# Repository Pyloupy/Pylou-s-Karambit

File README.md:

# Pylou-s-Karambit

Hey there ! This is the GitHub Repo where I'll show my creation based of the Reaver Karambit from Valorant (cf photo down below) that I wanted to bring to life!

I tried to make it as realistic as possible with LEDs A smoke generator and even movement and voice recognition!  You should see everything here that will make you able to recreate my work, GL :)
# Why ?
Well, you should first know that my work is completly useless and is purely aesthetic. It'll be able to cut butter at his peak or maybe set my house in fire if I did my job wrong ;-;

I wanted to make it as a fan of the game Valorant. A lot of recreation has been made because it is a very popular weapon skin in the game, but none tried to push the reality to the maximum, thats why I'm here !

At first, I created a prototype with not a lot of brain work behind it and it didnt work at all (as you can see in the photo) and I didn't even know why, so I gave up.

My friends made a little fun of me and that's why when I hear of the Fallout project I decided to take my revenge and make a clean work that will work! That's enough story telling, let's get in the details !
# Functionalities
Here's an exhaustive list of the functionnalities I implemented into my Karambit that maybe I'll extend later when completing the build!
- A rechargeable Smoke generator based on a E-cig
- RGB Show! With the help of an SK6812MINI and an acrylic tube to make special effects!
- Movement detection : A list of pre-trained movement to make different effects base on which movement you execute! 
- Edge AI Speech recogntion : A list of pre-trained word-orders to activate/desactivate certain functionalities using a custom-trained TinyML model via the PDM microphone
- Magnetic sensor : to detect if it is on his stand (more and that down below)
- Ultra-Low Power Management : Hardware-level Deep Sleep (SYSTEM OFF) implementation with QSPI flash memory shutdown and Wake-on-Motion via I2C intterupts, to save battery life.
- Hardware Fail-Safe: Native Watchdog Timer (WDT) implementation directly addressing the ARM Cortex-M4 to prevent software failure / thermal runaway

I really wanted to make this as complete as possible while keeping it the size of a real karambit that can fit in you hands, it was quite a challenge.
# Zine page
But an image is worth thousands of words! I made the CAD of my model in blender because the karambit is a really complex shape and I'm a lot more comfortable with blender even thought it's not really made for this job and I had to deal with some issues due to blender. 

But I made a little render with an exploded view effect and I think it turned out well:

The design is around the exploded view where you can see every components linked to the explanation of his role. I think it's a cool way to show off everything you have to fit in this tiny space to make it work!
For the text name, I tried to make an effect with the smoke comming out of the resistor, although I think the idea is great, I'm not completly happy with the effect it gives. But overall I'm happy with my zine page!  
If you want, In the CAD folder you can find the "render.blend" file where I worked on the exploded view if you want to play with it :)

# CAD
### the Karambit
Talking about CAD, as I said I did almost everything in Blender to work around the complex shape that the karambit is:

But I did use SOLIDWORKS when I had to model i couldn't find on the internet or to make a special adapter and then imported it in Blender.   
I think it is really more easy to work with it for placing components the way you want, and since I had so little space to work with it was perfect for me.  
I had to think about a way to:
- insert the pcb inside the handle
- fit the resistor inside the handle close the blade side and a good way to fix it
- make each part (2 handle part, 2 blade side) fit together with screw for a strong grip since you have to spin the karambit
- make a way to conduct light to the blade with no LEDs inside of it because the pcb couldn't go into the blade
- place usb-c port, reed sensor and cork hole for the tank in a way that is comfortable and make sense with the way it is held in the stand
Everything have his place and it's really not made randomely, I, in fact, made the pcb in the same time as the CAD files to rearange everything as I wanted to for optimal placement
### Stand
In the first place I wanted only to build the Karambit, but when I worked on the firmware, I realised that the board I selected didn't have a way to wake up itself throught the IMU.  
That's why I wanted a backup option for the wakeup system and I thought about a magnetic option with a stand. The idea is that when the karambit detects a magnet placed in the stand, It goes to sleep to save the battery, and when take it off it wakes up with special effects!

I wanted a dark and stylized way to show off the reaver karambit. With a bit of research I found this picture reference of the reaver woods from the game wayfinder that i didnt't even know existed:

<image src=./Pictures/ReaverWoods.png width=400>
  
I thought it completly matched the theme and made a model based on this reference image. It holds the knife with different branches and goes around like a protection.

<image src=./Pictures/Stand.png width=600>
  
I made it really big and I will have to print it in 5 different parts and glue it together, I really hope it will be strong enough to hold everything, but it should do the job.
### Adapters 

I also made some adapter in SOLIDWORKS to:
- Fix the resistor inside the handle
- Fix the pvc tube to the resistor
- Convert the airflow from the fan to the inside holes of the resistor

Thats is pretty much all for the CAD design

# PCB
Now for the PCB part! I did everything in Kicad which is a free software you can find [here](https://www.kicad.org/download/)
### Schematic
Overall, the schematic and electrical design is not really complicated as it consist only of the xiao nrf52840, pins for the battery, pins for the resistor, pins for the fan, 2 IRLZ44N mosfets and a couples of resistors and diode for protection.  
Here's the schematic:

<image src=./Pictures/Schematics.png width=800>
  
As you can see the mosfets control both the fan and resistor as the current could kill the microcontroller if connected directly to it.  
There are 10k pull-down resistors linked to the mosfets to prevent any unwanted turn on when the board is in deep sleep. The schottky 1N5819 diode is connected to the fan to prevent any back current that could fry the xiao board.

That is pretty much it, as I said nothing really complicated for the schematic, the hard part was to fit everything -->
### PCB design
Since the xiao boards include the charging system, IMU and microphone on itself, it really made the job easier.  
But the pcb itself is a bit small and in a strange shape since it had to fit in the curved form karambit.  
I think I couldn't really more include more components with the way I shaped the pcb, with the large trace I had to place for the current to flow easily into the heat resistor.
Here's how it looks:

I also added holes to scew the pcb to the handle of the karambit, and I used the mosfets holes to fix the battery beneath the pcb.  
The SK6812MINI LEDs is place as far away as I could to place it near the blade of the karambit, that is why the pcb has this strange L shape.  
You could see that there is two times pins for the battery. The first one on the left side is to connect it to the BT2.0 connector that my battery use for a proper connection. The second one inside the xiao nrf52 footprint is placed this way because the pins for the battery module inside the xiao board is beneath it, so it will be easier for the solder job to place it this way instead of directly connect it to the BT2.0 connector.  

I have to mention I choosed to use the DIP version of the board and not the SMD one because I'm still a beginner with soldering electronics and it is way more easier to do it this way. But a way of impromevement could be to use the SMD version to not have two little wires hanging between the pcb and the microcontroller.

I think there is some details I could improve on the pcb but I didn't want to make it to complex for a V1 of this project as I really want to make it work like a charm !
# Firmware
## Installation
### Arduino
You will have to get the [Arduino IDE](https://support.arduino.cc/hc/en-us/articles/360019833020-Download-and-install-Arduino-IDE) to flash the xiao board. Then you will have to install the Seeed Xiao board inside the Arduino IDE (tutorial [here](https://wiki.seeedstudio.com/XIAO_BLE/#getting-started)) and make sure you select the mbed boards and not the classic one!  
After that you will have to install a couples of arduino libraries that I worked with, I made a folder called "Librairies" that you can copy-paste into your local Arduino folder in what I believe is ```/username/Documents/Arduino/librairies``` / install zip libraries or simply get your own with the library manager inside arduino. There is a txt file with links to all of them.

Then you'll just have to open the ReaverFirmware.ino file select the xiao nrf52840 board (mbed version) and flash the firmware, this can take a while with the speech recognition compilation.
### Custom Speech Recognition
I already trained a model with my voice, but I'm not sure it'll respond to yours. That's why I made a tool to make your own dataset and train your own speech recognition model! First you'll have to flash the ```AudioRecordPC.ino```file to the xiao board.   
Then there is a python script to record directly from the xiao nrf52 microphone! You will have to install [python](https://www.python.org/downloads/) and the keyboard librarie first with this simple command: ```py -m pip install keyboard``` .  
Then modify in the script the name of your folder you want to get the dataset in, and the name of the first order you are recording. Record you first word press "r" and repeat. The more you do the better, I'll say minimum of 100 of them. Then press "q" to quit and save every file. 

Now you just have to follow this [tutorial](https://wiki.seeedstudio.com/XIAO-BLE-PDM-EI/) with you own dataset. Here's the parameters that I personnaly used and that is working great for me: <image src=>
Don't forget to change in the Firmware code the import of the library to your own !  
⚠️ I recommend you record you files after build (see below) to have more realistic conditions
### Movement Recognition
For this, we again will use Edge Impulse AI, basically just follow the steps of [this](https://wiki.seeedstudio.com/XIAOEI/) tutorial and create your own movements you want to recognize.
It is basically the same thing as the voice recognition but here, you can easely record your samples via the website and nodejs, that will have to install (but everything is shown on the tutorial)

In the Firmware Tools folder you will find a script that makes you able to test your model. It is just adapted from an exemple of the movement recogntion library. It is basically the same thing but without installing additional library and using the official Seeed Xiao Nrf52 LSM6DS3 library.

Again the compilation can take a while, be patient.

It is very basic, and I will work on a continuous version to make it smooth and non-blocking. (This is also true for voice recogntion, but in this case the model also needs to be optimized)

(PS: implementation in the main code hasn't been made yet, it'll be when I'll start building)

If you don't want complex movement recognition you could just use this bit of code to detect any type of fast movements with acceleration:
```cpp
//in the void loop:
  currentMillis = millis();
  float gX = myIMU.readFloatAccelX();
  float gY = myIMU.readFloatAccelY();
  float gZ = myIMU.readFloatAccelZ();

  float magnitude = sqrt(gX * gX + gY * gY + gZ * gZ);
  /* Serial.println(gX);
  Serial.println(gY);
  Serial.println(gZ); */
  // Detect rapid movement
  if (magnitude > 2.5) {
    Serial.println("slash detected");
    fumee(); //Function for effetcs/smoke
    //delay(1000);
    startMillis = millis();//restart timer coz movement detected
  }else{
    fumeeOff(); //Function to disable effects/smoke
  }
```
(It's the code written in the main loop Firmware for now)
## How does it work ?
For this part, I really wanted to do an advanced job and use all the potential that the xiao nrf52840 as to offer.  
I choosed to use Arduino code for this project as it is efficient and well more documented than the other programming language options.  

There is a couple of files that is in the firmware folder, and I tried to comment everything on the way they work if you want to take a closer look!
Most of these folders are the firmware divided in multiples part to test every functionality of the firmware separetely:
- Testing the Deep Sleep mode and the different way to wake it up (IMU or reed sensor)
- Testing the Voice recognition model and the different way to use it (Continuous or no)
- Testing the watchdog (natively implemented inside the nrf52 chip from Nordic Semiconductor, this was a bit complicated to make it work) to prevent any errors crashing with the voice AI model
- Battery reading test
- IMU testing
- Fan/Led/mosfets testing
These scripts could help you when building the Karambit to check every components and maybe find what isn't working (if it's not working) especially with voice and movement recognition and maybe calibrate the battery reading, Deep Sleep and watchdog should work perfectly.

Have fun creating new effects/movement/orders to you karambit to make it personal!
#BOM
Now here's the BOM or aka how to get your components.  
There is link for everything mainly using Aliexpress. I personaly took the resistor with a French reseller so maybe you'll have to look somewhere else, (just search the model name).  
For paint, I took mine in a local store, be free to pick any colour you want to make your favorite variant of the reaver karambit!  
I ordered my pcb on Jlcpcb, it is great and cheap. For filament I used what I already had, but take whatever you want, it's best if it is strong and heat resistant.  
Careful for prices they may vary over time, Aliexpress is very volatile with there prices

Here's the BOM (you can also find it in CSV and xlsx format in the files):
| Item | Specs | Quantity | Buying Price(€) | Unit Price| Total Price (€) | Link | Tips |
| ---- | ----- | -------- | --------------- | --------- | --------------- | ---- | ---- |
| 18x14mm fan | 0.2 cfm, blow the smoke as it is in a closed case | 1 | 4.29 | 4.29 | 4.29 | [Link](https://fr.aliexpress.com/item/1005010476941631.html) | |
| 1N5819 Diode | Reverse polarity protection for the fan | 1 | 1.33 | 0.0248 | 0.0248 | [Link](https://fr.aliexpress.com/item/1005001552094086.html) | Others diodes will work, check the specs and measurement |     
| 100x2mm acrylic tube | Conduct the light into the blade | 1 | 1.8 | 0.171 | 0.171 | [Link](https://fr.aliexpress.com/item/1005005536829247.html) |  |
| M2xL2xOD3.2 insert | to fix the blade the the handle | 5 | 1.9 | 0.019 | 0.095 | [Link](https://fr.aliexpress.com/item/1005006472702418.html) | It'll be cheaper to just buy a kit of different type of inserts |
| M2xL4xOD3,2 insert | to fix the 2 parts of the knife together | 6 | 2.25 | 0.0225 | 0.135 | [Link](https://fr.aliexpress.com/item/1005006472702418.html) |  |
| M3xL5xOD4,2 insert | to fix the pcb via the transistors holes | 3 | 1.82 | 0.0364 | 0.1092 | [Link](https://fr.aliexpress.com/item/1005006472702418.html) |  |
| Battery BETAFPV LAVA II 1S 480mah | LiHv with 95C rating to ensure enough current | 1 | 15.29 | 3.54 | 3.54 | [Link](https://fr.aliexpress.com/item/1005010775720329.html) | Other batteries could work just be sure the C rating is high enough (hard to check on most Aliexpress battery where only fpv drones C rating are precised) |
| Reed switch NC  | Low voltage GPS-23 (act as a sensor to detect if it's in the stand) | 1 | 5.79 | 5.79 | 5.79 | [Link](https://fr.aliexpress.com/item/1005006926125113.html) |  |
| Seeed Studio Xiao nRF52840 Sense | 64 Mhz processor, IMU and microphone integrated | 1 | 18.19 | 18.19 | 18.19 | [Link](https://fr.aliexpress.com/item/1005006988944671.html) |  |
| BT 2.0 male cable | to cleanly connect the battery to the pcb | 1 | 3.59 | 1.945 | 1.945 | [Link](https://fr.aliexpress.com/item/1005009623841974.html) |  |
| SK6812MINI LED | 35 35 ARGB Led  | 1 | 10.89 | 0.1089 | 0.1089 | [Link](https://fr.aliexpress.com/item/1005004931260882.html) | You should modify the pcb and take SK6812MINI-E (the E is important) It's a lot more easier to solder, I already have those so i will use them (in pain) |
| GS Air Eleaf Clearomizer | 2.5 ml tank / 1,5 ohm coil (included) | 1 | 7.5 | 7.5 | 7.5 | [Link](https://www.oliquide.com/Clearomiseurs-Eleaf-Eleaf-GS-Air.) |  |
| Transistor IRLZ44N | 47A max, Vgs=2V, to control both fan and heat coil | 2 | 2.06 | 0.206 | 0.412 | [Link](https://fr.aliexpress.com/item/1005009876208141.html) | Should be overkill, I took them coz I already had them |
| 6mm diameter PVC Tube | 6mm exterior diameter 4mm interior diameter, to conduct the smoke to the blade | 1 | 2.09 | 2.09 | 2.09 | [Link](https://fr.aliexpress.com/item/1005006173546510.html) |  |
| M2 Screws | Screws different lengths kit | 1 | 5.09 | 5.09 | 5.09 | [Link](https://fr.aliexpress.com/item/1005007278965396.html) | Might have to cut them, make sure to put a bolt before to not break the thread |
| Magnet | 8mm diameter | 1 | 3.59 | 0.07 | 0.07 | [Link](https://fr.aliexpress.com/item/1005011969218794.html) |  |
| Anti-slip pads | for the stand | 7 | 1.8 | 0.018 | 0.12 | [Link](https://fr.aliexpress.com/item/1005008980666002.html) |  |
| 200/1K Ω resistors | for transistor signal and pull-down | 2 each |  |  |  | Take any kit of resistors on Aliexpress it'll be useful in the future |  |
| Hyper CF PLA Filament | For printing the handles, blades, stand and adaptaters | 1 | 34.99 | 34.99 | 34.99 | [Link](https://store.creality.com/fr/products/hyper-pla-cf-carbone-fibre-1-75mm-filament-dimpression-3d-1kg) | It's just what I will be using coz i have it in stock, but anything can do the job ABS will be better for heat coil |
| Fake Leather | Auto-adhesive layer | 1 | 4.99 | 4.99 | 4.99 | [Link](https://fr.aliexpress.com/item/1005008381916334.html) |  |
| Mettalic Paint | Shiny paint weeee | 1 | 5 | 5 | 5 | Bought from local store |  |
| Red Metallic Paint | Shiny paint weeee | 1 | 5 | 5 | 5 | Bought from local store |  |
| PCB | 1.6mm two layers | 1 | 3 | 0.6 | 0.6 | Got it from jlcpcb but use whats cheaper in your region (jlcpcb is a great choice tho) |  |
| Shipping Price |  | ~10-15€ |  |  |  |  |  |
| Total Price |  | 109.55€ | 128.88$ |  |  |  |  |
| Total Buying Price (Because you'll buying multiples at once) |  | 150.45€ | 177$  |  |  |  |  |

# Build time !
It's now time to make the Karambit! If you're confused any time, be free to check the blender file to understand where everything is placed! Everything is named and (more or less) organized, I hope you'll understand everything :)

### **Step 1:** Printing

First print everything from the STLs folder with your filament, it should be around 800g gram worth of filament, (I hope for you that everything fits in your printer, for reference mine is an ender 3 V3 KE).  

⚠️ Be careful when printing the stand, you will have to stop the print at a certain height to insert the magnet inside the branches and then resume print.
Then glue everything together for the stand, sand it and paint it if you think that is necessary. I recommend you to do it at least for the Karambit parts to make it cleaner!
Don't forget to place the anti-slip pads below the stand for a stable structure!
Place the fake leather into both handles, mines auto-adhesive if you take the one linked in the BOM

### **Step 2** soldering:

Beforehand be careful with the reed sensor, you will have to cut a platic part from it : 

without that it won't fit.  
Solder the xiao nrf52840 (dont forget connection for the battery), 200/1k ohms resistor, both mosfets, battery cable, fan, Schottky diode, SK6812MINI Led and Reed switch (let enough cable to play with) into the PCB and test everything with the different scripts in the Firmware folder.  

With a soldering Iron place the differents inserts in there places.  

Drill a 6mm hole into the Resistor's tank (check alignement with the hole made in the blade) and glue the tube to the tank with a waterproof glue like epoxy (will add a picture on that when i'll do it)
Solder + and - 18awg or less cable to the resistor as it shows on this image(then solder it to the PCB with enough length to play with):  (will add a picture on that when i'll do it)

### Step 3: assembling:
Fix the battery below the PCB with the adpater and screws/bolt.  
Fix the PCB into the handle with the scews.  
Fix the Resistor with the adapter printed and screws. (Careful for the orientation !) (PS: photo's comming when ill finish build)
Fix the Fan Adapter to the fan when screwing the fan.

Take the joint from the part you removed earlier from the clearomizer and place it on the adapter, then put it with the 6mm tube into the resistor. 

Then block the left side of the base to force the airflow to go throught the coil : 

Fix the first blade to the handle.

Cut and insert the acrylic tube into the handle and place it above the LED, if it doesn't transmit light good enough, try sanding the sides of the acrylic tube.  
Fix the reed switch to the handle.

Finally fix the other blade to the other handle and fix both handles together, upload the firmware when you are sure everything works and you're good to go!

# Special Thanks !

Thanks to my boy Carabouille for participating with me and qualify before me (bravo!)

Thanks to the Hack Club community for this incredible opurtinty that represent fallout!

Thanks to the UwU GanG to exist and be the best RL team imaginable :).

Thanks to Seeed Studio for the xiao boards (cyu in Shenzhen, plzzzzzz make more exemples code on your board ty)

Thanks to Emmanuel Macron for giving me so much money in scolarship, the goat
<br/>
<br/>
<br/>

See you in Shenzhen ;).

<br/>
<br/>
<br/>

\- Pylou

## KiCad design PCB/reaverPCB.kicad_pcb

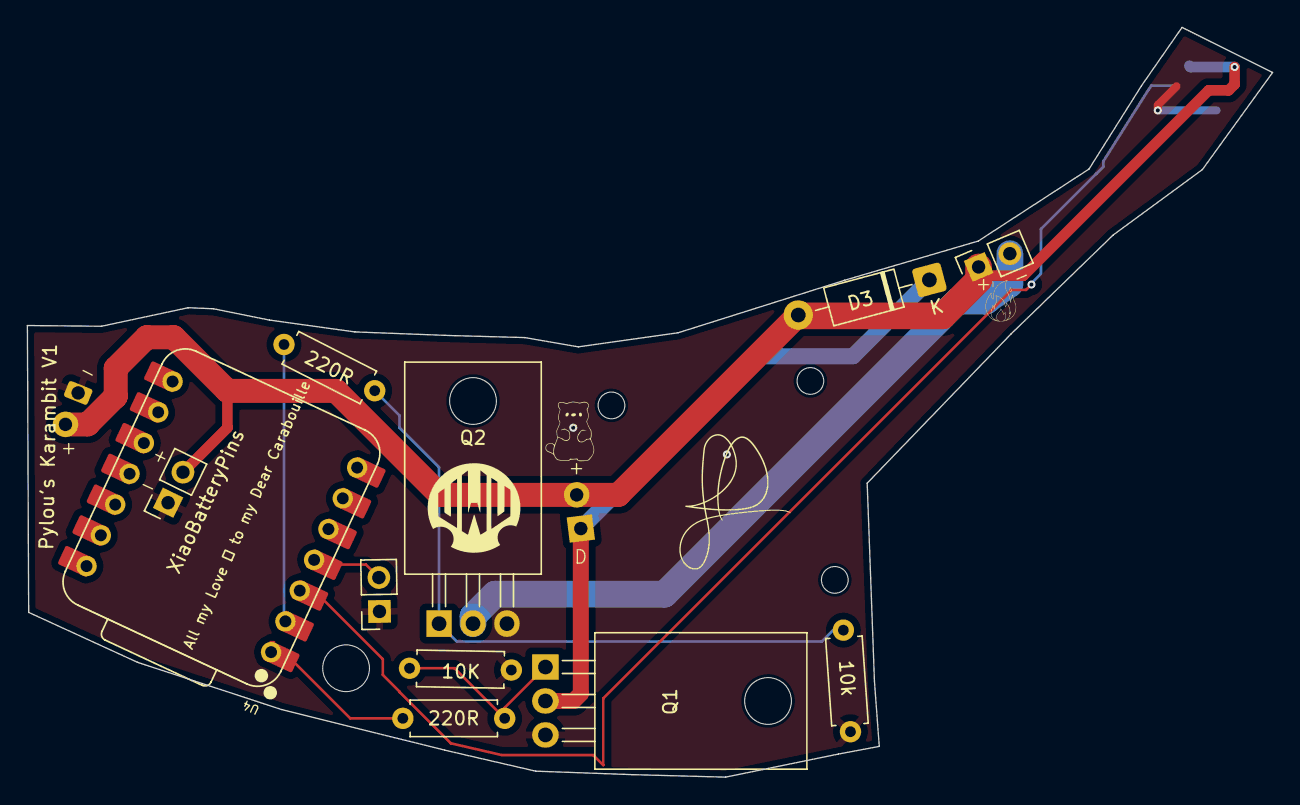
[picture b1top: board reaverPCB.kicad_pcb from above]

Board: 2 copper layers, 93.2 x 56.1 mm, 14 parts (1 on the bottom side), 10 nets.

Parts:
10k: 10K; R_Axial_DIN0207_L6.3mm_D2.5mm_P7.62mm_Horizontal
D1: SK6812MINI; LED_SK6812MINI_PLCC4_3.5x3.5mm_P1.75mm
D3: 1N5819; D_DO-41_SOD81_P10.16mm_Horizontal
EHead1: Conn_01x02_Socket; PinSocket_1x02_P2.54mm_Vertical
Q1: Fan; TO-220-3_Horizontal_TabDown
Q2: EHead; TO-220-3_Horizontal_TabDown
R2: 10K; R_Axial_DIN0207_L6.3mm_D2.5mm_P7.62mm_Horizontal
R3, R4: 220R; R_Axial_DIN0207_L6.3mm_D2.5mm_P7.62mm_Horizontal
ReedSwitch1: Conn_01x02_Socket; PinSocket_1x02_P2.54mm_Vertical
U2: Fan18184
U3: 480mah
U4: XIAO-nRF52840-DIP
XiaoBatteryPins: Conn_01x02_Socket; PinSocket_1x02_P2.54mm_Vertical

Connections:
EHEAD_PIN: R3.1, U4.2 (P0.03_A1_D1)
FAN_PIN: R4.1, U4.1 (P0.02_A0_D0)
GND: 10k.1, D1.2 (VSS), Q1.3 (S), Q2.3 (S), R2.1, ReedSwitch1.1, U3.1 (GND), XiaoBatteryPins.1
LED_PIN: D1.3 (DIN), U4.3 (P0.28_A2_D2)
unnamed: D3.1 (K), Q1.2 (D), U2.2 (GND)
unnamed: EHead1.2, Q2.2 (D)
unnamed: Q1.1 (G), R2.2, R4.2
unnamed: 10k.2, Q2.1 (G), R3.2
PinReed: ReedSwitch1.2, U4.4 (P0.29_A3_D3)
VBATT: D1.4 (VDD), D3.2 (A), EHead1.1, U2.1 (VCC), U3.2 (VCC), XiaoBatteryPins.2

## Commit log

2026-06-06 Enhance README with project details and functionalities
    Expanded the README to include more details about the project, its functionalities, and the motivation behind creating the Reaver Karambit replica.
2026-06-07 Improve README formatting and readability
    Refactor README content for clarity and structure.
2026-06-07 Update README to include build time section
    Added a section for build time in the README.
2026-06-07 Fix spelling and clarity issues in README.md
    Corrected spelling errors and improved clarity in the README.
2026-06-09 Create dumbfile
2026-06-09 Ajout de MainModel et Render
2026-06-11 Include movement detection code in README
    Added code snippet for detecting fast movements using acceleration.
2026-06-11 Update README with movement recognition details
    Clarify movement recognition instructions and update code reference.
2026-06-11 Update README with future work notes
    Added notes about future improvements for basic functionality and voice recognition optimization.
2026-06-11 Update BOM.csv with duplicate entries
    Added duplicate entries for Hyper CF PLA Filament and Fake Leather while removing Hyper CF PLA Filament and Fake Leather from the original list.
